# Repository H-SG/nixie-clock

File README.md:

# Nixie Clock
Since I first discovered Nixie tubes in the early 2000s I've been fascinated by them and have always wanted to own a Nixie clock. Well, what better way than to build one yourself? Due to cost and cuteness, I've gone with the smallest Nixie tubes commonly available, IN-17s.

I seriously started doing the design for this around 2017 to distract myself from my thesis, and after making a rudimentary PCB in Eagle and a 2 tube breadboard prototype the project languished until 2023.

## Design
I'm going for a sandwich PCB design which I can do in stages to play around with various control schemes and other options. I'm going for a relatively standard approach of 74141 drivers, 74595 shift registeres, high side anode control for dimming, and an Arduino running it all with a mostly through-hole design. There are better ways with more modern components, but I'm doing this for A E S T H E T I C.

### Board 1 - Nixie Drivers
The first (and so far only) PCB made, this is where the Nixie tubes are soldered to along with the driver chips and anode current limiting resistors. I've had to make a few custom footprints in kicad since Eagle has gone the way of the dodo, but I really enjoyed this process.

Future revisions will probalby include the following improvements:
* Tighter layout of tubes
* Some rail capacitance
* Silkscreen on back?

## Code
It's relatively straightforward.
1. Get time from RTC module
2. Shift out time to 74595s
3. Do some fun dimming control
4. Repeat

I almost did some nasty stuff with pointers, and then decided I don't need that in my life. I might look at increasing PWM frequency for brightness control in future, but currently it works quite well.

## References
I stand on the shoulders of others, here are all the references I used for this project:
* [Dalibor's guidance on preventing cathode poisoning](https://www.manula.com/manuals/daliborfarny-com/nixie-tubes/1/en/topic/cathode-poisoning-prevention-routine)
* [High side driving with optoisolators](https://www.microfarad.de/nixie-clock/#gallery-10)
* [TLP627 datasheet](https://www.soemtron.org/downloads/disposals/tlp627.pdf)
    * [Local supplier](https://www.mantech.co.za/ProductInfo.aspx?Item=35M5983)
* [High side driving with MPSA92 & 42](https://reipooom.files.wordpress.com/2011/08/nixie-clock-from-jameco1.pdf)
    * [More arguments about this](https://electronics.stackexchange.com/questions/331220/anode-driver-for-nixie-clock)
* [Reference info on IN-17](https://www.swissnixie.com/tubes/IN17/)
* [Shift registers on Arduino](https://docs.arduino.cc/tutorials/communication/guide-to-shift-out)
* [Possible source for Soviet era 74141 drivers](https://tubehobby.com/show_det.php?det=35)
    * These use 2.5mm pinspacing instead of 2.54mm (1mili)
    * Modern sources are Integral from Belarus...

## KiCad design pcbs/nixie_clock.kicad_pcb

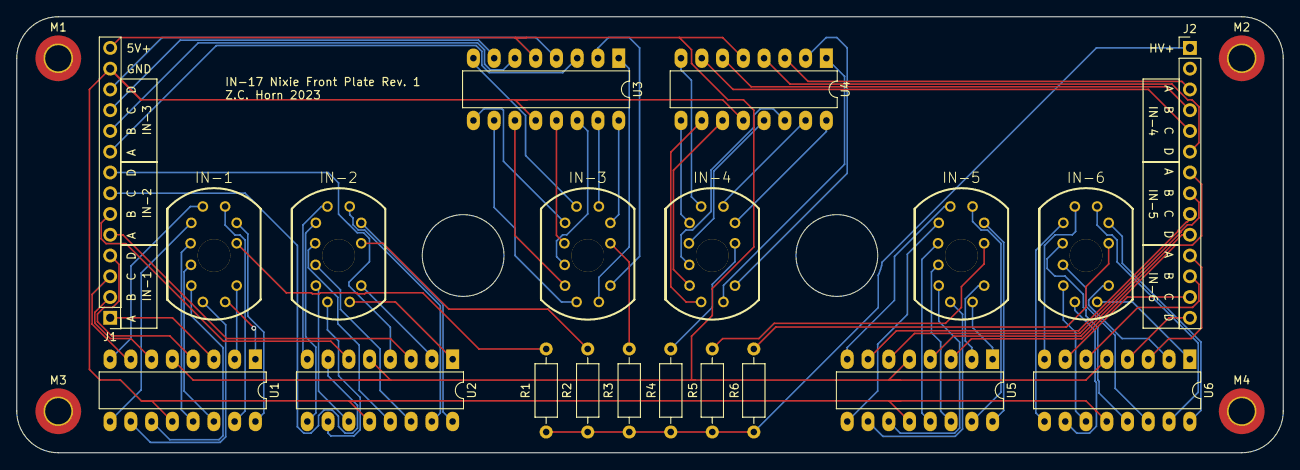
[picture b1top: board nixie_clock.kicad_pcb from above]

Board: 2 copper layers, 154.9 x 53.3 mm, 24 parts (0 on the bottom side), 93 nets.

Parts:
IN-1, IN-2, IN-3, IN-4, IN-5, IN-6: nixies-us-IN-17
J1, J2: Conn_01x14_Pin; PinHeader_1x14_P2.54mm_Vertical
M1, M2, M3, M4: MountingHole_3.2mm_M3_DIN965_Pad_TopBottom
R1, R2, R3, R4, R5, R6: 22k; R_Axial_DIN0207_L6.3mm_D2.5mm_P10.16mm_Horizontal
U1, U2, U3, U4, U5, U6: 74141; DIP-16_W7.62mm_LongPads

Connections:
/Vcc: J1.14, U1.5 (VCC), U2.5 (VCC), U3.5 (VCC), U4.5 (VCC), U5.5 (VCC), U6.5 (VCC)
/gnd: J1.13, U1.12 (GND), U2.12 (GND), U3.12 (GND), U4.12 (GND), U5.12 (GND), U6.12 (GND)
/hv1: IN-1.A, R1.1
/hv2: IN-2.A, R2.1
/hv3: IN-3.A, R3.1
/hv4: IN-4.A, R4.2
/hv5: IN-5.A, R5.2
/hv6: IN-6.A, R6.2
/nixie-anodes: J2.1, R1.2, R2.2, R3.2, R4.1, R5.1, R6.1
unnamed: J1.1, U1.3 (A)
unnamed: J1.2, U1.6 (B)
unnamed: J1.3, U1.7 (C)
unnamed: J1.4, U1.4 (D)
unnamed: J1.5, U2.3 (A)
unnamed: J1.6, U2.6 (B)
unnamed: J1.7, U2.7 (C)
unnamed: J1.8, U2.4 (D)
unnamed: J1.9, U3.3 (A)
unnamed: J1.10, U3.6 (B)
unnamed: J1.11, U3.7 (C)
unnamed: J1.12, U3.4 (D)
unnamed: J2.3, U4.3 (A)
unnamed: J2.4, U4.6 (B)
unnamed: J2.5, U4.7 (C)
unnamed: J2.6, U4.4 (D)
unnamed: J2.7, U5.3 (A)
unnamed: J2.8, U5.6 (B)
unnamed: J2.9, U5.7 (C)
unnamed: J2.10, U5.4 (D)
unnamed: J2.11, U6.3 (A)
unnamed: J2.12, U6.6 (B)
unnamed: J2.13, U6.7 (C)
unnamed: J2.14, U6.4 (D)
unnamed: IN-1.0, U1.16 (~Q0)
unnamed: IN-1.1, U1.15 (~Q1)
unnamed: IN-1.2, U1.8 (~Q2)
unnamed: IN-1.3, U1.9 (~Q3)
unnamed: IN-1.4, U1.13 (~Q4)
unnamed: IN-1.5, U1.14 (~Q5)
unnamed: IN-1.6, U1.11 (~Q6)
unnamed: IN-1.7, U1.10 (~Q7)
unnamed: IN-1.8, U1.1 (~Q8)
unnamed: IN-1.9, U1.2 (~Q9)
unnamed: IN-2.0, U2.16 (~Q0)
unnamed: IN-2.1, U2.15 (~Q1)
unnamed: IN-2.2, U2.8 (~Q2)
unnamed: IN-2.3, U2.9 (~Q3)
unnamed: IN-2.4, U2.13 (~Q4)
unnamed: IN-2.5, U2.14 (~Q5)
unnamed: IN-2.6, U2.11 (~Q6)
unnamed: IN-2.7, U2.10 (~Q7)
unnamed: IN-2.8, U2.1 (~Q8)
unnamed: IN-2.9, U2.2 (~Q9)
unnamed: IN-3.0, U3.16 (~Q0)
unnamed: IN-3.1, U3.15 (~Q1)
unnamed: IN-3.2, U3.8 (~Q2)
unnamed: IN-3.3, U3.9 (~Q3)
unnamed: IN-3.4, U3.13 (~Q4)
unnamed: IN-3.5, U3.14 (~Q5)
unnamed: IN-3.6, U3.11 (~Q6)
unnamed: IN-3.7, U3.10 (~Q7)
unnamed: IN-3.8, U3.1 (~Q8)
unnamed: IN-3.9, U3.2 (~Q9)
unnamed: IN-4.0, U4.16 (~Q0)
unnamed: IN-4.1, U4.15 (~Q1)
unnamed: IN-4.2, U4.8 (~Q2)
unnamed: IN-4.3, U4.9 (~Q3)
unnamed: IN-4.4, U4.13 (~Q4)
unnamed: IN-4.5, U4.14 (~Q5)
unnamed: IN-4.6, U4.11 (~Q6)
unnamed: IN-4.7, U4.10 (~Q7)
unnamed: IN-4.8, U4.1 (~Q8)
unnamed: IN-4.9, U4.2 (~Q9)
unnamed: IN-5.0, U5.16 (~Q0)
unnamed: IN-5.1, U5.15 (~Q1)
unnamed: IN-5.2, U5.8 (~Q2)
unnamed: IN-5.3, U5.9 (~Q3)
unnamed: IN-5.4, U5.13 (~Q4)
unnamed: IN-5.5, U5.14 (~Q5)
unnamed: IN-5.6, U5.11 (~Q6)
unnamed: IN-5.7, U5.10 (~Q7)
unnamed: IN-5.8, U5.1 (~Q8)
unnamed: IN-5.9, U5.2 (~Q9)
unnamed: IN-6.0, U6.16 (~Q0)
unnamed: IN-6.1, U6.15 (~Q1)
unnamed: IN-6.2, U6.8 (~Q2)
unnamed: IN-6.3, U6.9 (~Q3)
unnamed: IN-6.4, U6.13 (~Q4)
unnamed: IN-6.5, U6.14 (~Q5)
unnamed: IN-6.6, U6.11 (~Q6)
unnamed: IN-6.7, U6.10 (~Q7)
unnamed: IN-6.8, U6.1 (~Q8)
unnamed: IN-6.9, U6.2 (~Q9)

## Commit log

2023-09-30 Initial commit of all artefacts
2023-09-30 Added references
